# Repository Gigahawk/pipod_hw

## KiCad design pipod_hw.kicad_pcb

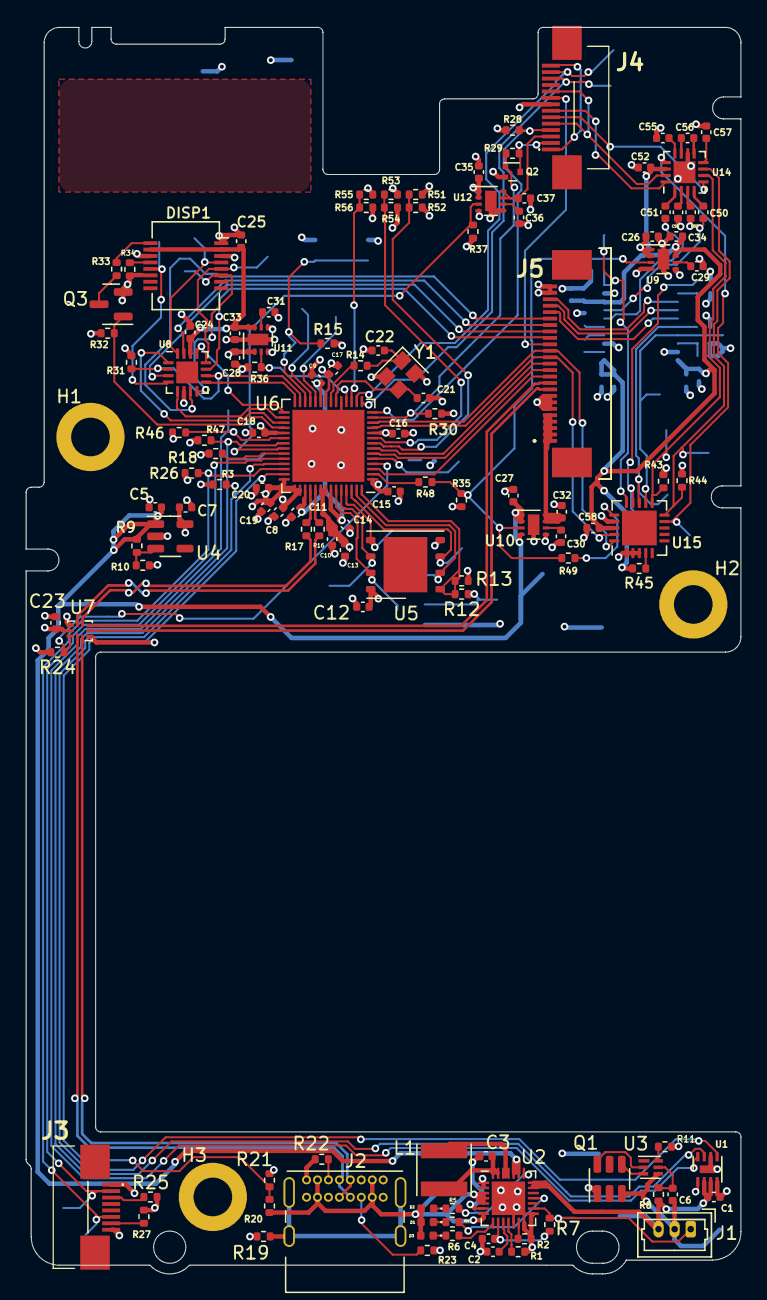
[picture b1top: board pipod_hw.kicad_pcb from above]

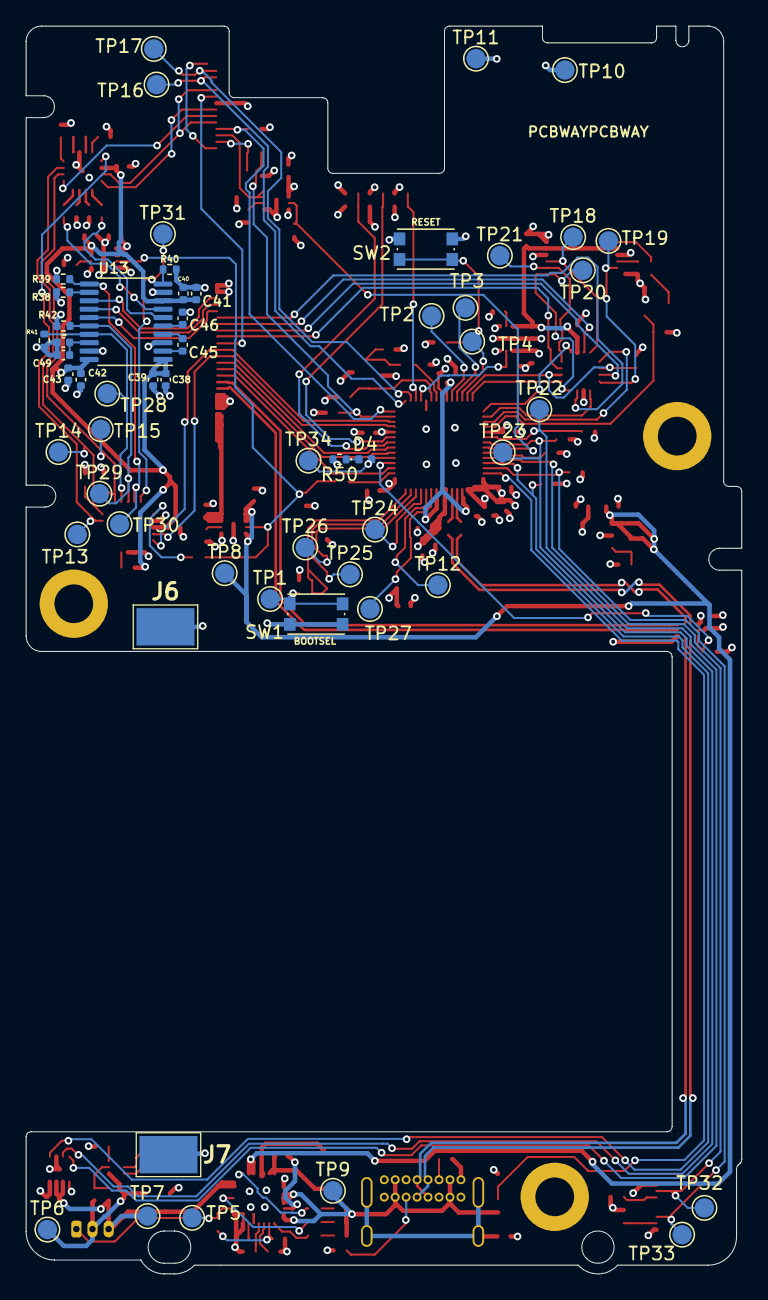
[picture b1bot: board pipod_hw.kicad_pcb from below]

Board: 4 copper layers, 55.5 x 96.8 mm, 184 parts (56 on the bottom side), 136 nets.

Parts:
C1, C3, C6, C8, C9, C10, C11, C12, C13, C15, C16, C17, C18, C19, C23, C24, C39, C41, C43, C49, C58: 100n; C_0402_1005Metric
C2: 150n; C_0402_1005Metric
C4, C14, C20, C50, C51, C53, C54, C55, C56, C57: 1u; C_0402_1005Metric
C5, C7, C25, C26, C27, C28, C32, C33, C34, C35, C37, C38, C40, C42, C48: 10u; C_0402_1005Metric
C21, C22: 30p; C_0402_1005Metric
C29, C30, C31, C36: DNI; C_0402_1005Metric
C45, C46, C52: 2.2u; C_0402_1005Metric
D1: RED; LED_0402_1005Metric
D2: BLU; LED_0402_1005Metric
D3, D4: GRN; LED_0402_1005Metric
DISP1: STP240320_0200B; Molex_SlimStack_54722-0164_2x08_P0.50mm_Vertical
H1, H2, H3: 9774040243R
J1: Conn_01x03_Male; Molex_PicoBlade_53047-0310_1x03_P1.25mm_Vertical
J2: USB_C_Receptacle_USB2.0; USB_C_Receptacle_GCT_USB4085
J3: SFV8R-2STE1HLF; SFV8R2STE1HLF
J4: SFV14R-2STE1HLF; SFV14R2STE1HLF
J5: 2-1734839-5; 217348395
J6, J7: S7051-42R; S705142R
L1: 1u; L_Vishay_IFSC-1515AH_4x4x1.8mm
LOGO1: Logo_Open_Hardware_Large; OSHW-Logo2_9.8x8mm_Mask
Q1: DMG9926UDM; SOT-23-6
Q2: NTK3139PT1G; SOT-723
Q3: BSS138; SOT-23
R1: 5.9k 2%; R_0402_1005Metric
R2: 1.6k; R_0402_1005Metric
R3, R7, R9, R13, R15, R18, R20, R24, R25, R27, R28, R30, R31, R32, R34, R35, R36, R37, R38, R39, R40, R41, R42, R43, R44, R45, R46, R47, R52, R54, R56: 10k; R_0402_1005Metric
R4, R5, R6, R12, R14, R48, R49: 1k; R_0402_1005Metric
R8: 330R; R_0402_1005Metric
R10, R29, R51, R53, R55: DNI; R_0402_1005Metric
R11: 2.2k; R_0402_1005Metric
R16, R17: 27R; R_0402_1005Metric
R19: DNP; R_0402_1005Metric
R21: 15k; R_0402_1005Metric
R22, R23: 5.1k; R_0402_1005Metric
R26: 100k; R_0402_1005Metric
R33: 10R; R_0402_1005Metric
R50: 470R; R_0402_1005Metric
SW1, SW2: SW_Push; SW_Push_1P1T_NO_CK_KMR2
TP1, TP2, TP3, TP4, TP5, TP6, TP7, TP8, TP9, TP10, TP11, TP12, TP13, TP14, TP15, TP16, TP17, TP18, TP19, TP20, TP21, TP22, TP23, TP24, TP25, TP26, TP27, TP28, TP29, TP30, TP31, TP32, TP33, TP34: TestPoint; TestPoint_Pad_D1.5mm
U1: MAX17048G+T10; DFN-8-1EP_2x2mm_P0.5mm_EP0.6x1.2mm
U2: MAX8903AETI+T; QFN-28-1EP_4x4mm_P0.4mm_EP2.6x2.6mm
U3: BQ29728DSER; WSON-6_1.5x1.5mm_P0.5mm
U4: XC6210B332MR; SOT-23-5
U5: W25Q128JVS; WSON-8-1EP_6x5mm_P1.27mm_EP3.4x4.3mm
U6: RP2040; QFN-56-1EP_7x7mm_P0.4mm_EP5.6x5.6mm
U7: NLAS7242MUTBG; UQFN-10_1.4x1.8mm_P0.4mm
U8: RS2299XTQC16; QFN-16-1EP_3x3mm_P0.5mm_EP1.7x1.7mm
U9, U10, U11, U12: TPS22965TDSGRQ1; WSON-8-1EP_2x2mm_P0.5mm_EP0.9x1.6mm
U13: PCM5102APWR; TSSOP-20_4.4x6.5mm_P0.65mm
U14: PAM8908JER; QFN-16-1EP_3x3mm_P0.5mm_EP1.7x1.7mm
U15: MCP23008-E/ML; QFN-20-1EP_4x4mm_P0.5mm_EP2.7x2.7mm
Y1: 12MHz 20pF; Crystal_SMD_2520-4Pin_2.5x2.0mm

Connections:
+1V1: C9.2, C11.2, C14.2, U6.23 (DVDD), U6.45 (VREG_VOUT), U6.50 (DVDD)
+3V3: C7.1, C8.2, C10.2, C12.2, C13.2, C15.2, C16.2, C17.2, C18.2, C19.2, C20.2, C23.1, C26.2, C28.2, C35.2, J3.1, Q2.2 (S), R3.1, R13.2, R15.1, R24.2, R25.2, R26.2, R27.2, R28.2, R30.1, R46.1, R47.1, R51.1, R53.1, R55.1, TP10.1, U4.5 (VOUT), U5.8 (VCC), U6.1 (IOVDD), U6.10 (IOVDD), U6.22 (IOVDD), U6.33 (IOVDD), U6.42 (IOVDD), U6.43 (ADC_AVDD), U6.44 (VREG_IN), U6.48 (USB_VDD), U6.49 (IOVDD), U7.9 (VCC), U9.1 (VIN), U9.2 (VIN), U9.4 (VBIAS), U11.1 (VIN), U11.2 (VIN), U11.4 (VBIAS), U12.1 (VIN), U12.2 (VIN), U12.4 (VBIAS)
+BATT: C1.2, J1.3, R8.1, TP7.1, U1.2 (CELL), U1.3 (VDD), U2.20 (BAT), U2.21 (BAT)
-BATT: C6.2, J1.2, Q1.3 (S2), TP6.1, U3.4 (VSS)
/Audio/AMP_CAP+: C56.1, U14.11 (CAP+)
/Audio/AMP_CAP-: C56.2, U14.9 (CAP-)
/Audio/AMP_HPVDD: C55.2, U14.12 (HPVDD)
/Audio/AMP_HPVSS: C57.1, U14.8 (HPVSS)
/Audio/AMP_INL+: C54.2, U14.2 (INL+)
/Audio/AMP_INL-: C51.2, U14.1 (INL-)
/Audio/AMP_INR+: C53.2, U14.3 (INR+)
/Audio/AMP_INR-: C50.2, U14.4 (INR-)
/Audio/DAC_CAPM: C45.2, U13.4 (CAPM)
/Audio/DAC_CAPP: C45.1, U13.2 (CAPP)
/Audio/DAC_LDOO: C48.1, C49.1, U13.18 (LDOO)
/Audio/DAC_SCK: R38.2, U13.12 (SCK)
/Audio/DAC_VNEG: C46.1, U13.5 (VNEG)
/Display/DISP_BL_MOS_D: Q3.3 (D), R33.1
/Display/DISP_CS: DISP1.8 (CS), R34.1
/Display/DISP_LEDK: DISP1.2 (LEDK), R33.2
/Headphone/HP_CLICKER_SPEAKER: J4.2, Q2.3 (D), R29.2
/Load Switches/AUDIO_SW_CT: C29.2, U9.6 (CT)
/Load Switches/DISP_SW_CT: C31.2, U11.6 (CT)
/Load Switches/PI_SW_CT: C30.2, U10.6 (CT)
/Load Switches/RMT_SW_CT: C36.2, U12.6 (CT)
/Pi/PI_VCC_LATCH: R49.1, U15.16 (GP7)
/Pi/~IO_EX_RST: R45.2, U15.4 (~RESET)
/Power/CHRG_BST: C3.2, U2.6 (BST)
/Power/CHRG_CS: L1.1, U2.25 (CS), U2.26 (CS)
/Power/CHRG_CURR_SET: R2.2, U2.13 (ISET)
/Power/CHRG_DOK_LEDK: D3.1 (K), R6.1
/Power/CHRG_FLT_LEDK: D1.1 (K), R4.1
/Power/CHRG_IN_CURR_SET: R1.2, U2.11 (IDC)
/Power/CHRG_LEDK: D2.1 (K), R5.1
/Power/CHRG_LX: C3.1, L1.2, U2.27 (LX), U2.28 (LX)
/Power/CHRG_TIMER_SET: C2.2, U2.10 (CT)
/Power/CHRG_VL: C4.2, R7.1, U2.9 (VL)
/Power/PROT_BAT+: C6.1, R8.2, U3.5 (BAT)
/Power/PROT_C: Q1.6 (G1), U3.2 (Cout)
/Power/PROT_D: Q1.4 (G2), U3.3 (Dout)
/Power/PROT_V-: R11.2, U3.6 (V-)
/SMC/PI_VCC_EN: R48.2, U6.2 (GPIO0)
/SMC/SMC_SWCLK: TP2.1, U6.24 (SWCLK)
/SMC/SMC_SWD: TP3.1, U6.25 (SWD)
/SMC/SMC_USB_D+: R16.2, U6.47 (USB_DP)
/SMC/SMC_USB_D-: R17.2, U6.46 (USB_DM)
/SMC/SMC_XIN: C21.2, U6.20 (XIN), Y1.3
/SMC/SMC_XOUT: R14.1, U6.21 (XOUT)
/SMC/SMC_XOUT_ATTN: C22.1, R14.2, Y1.1
/SMC/~SMC_CW_CS: R18.1, U6.37 (GPIO25)
/SMC/~SMC_USB_BOOT: R12.1, SW1.2, TP1.1
/USB/USB_SHIELD: J2.S1 (SHIELD), R19.2
AUDIO_3V3: C34.2, C38.1, C39.1, C40.1, C41.1, C42.1, C43.1, C52.2, C58.2, R45.1, U9.7 (VOUT), U9.8 (VOUT), U13.1 (CPVDD), U13.8 (AVDD), U13.20 (DVDD), U14.14 (PVDD), U15.18 (VDD)
CW_EN1: J3.3, R25.1
CW_EN2: J3.7, R27.1
DAC_OUTL: C51.1, U13.6 (OUTL)
DAC_OUTR: C50.1, U13.7 (OUTR)
DISP_3V3: C24.2, C25.1, C33.2, DISP1.3 (LEDA), DISP1.4 (VCC), U8.14 (V+), U11.7 (VOUT), U11.8 (VOUT)
DISP_3V3_EN: R36.2, U6.18 (GPIO15), U11.3 (ON)
DISP_DC: DISP1.7 (WR/A0), TP18.1, U8.16 (COM1)
DISP_INPUT_SEL: R31.2, U6.27 (GPIO16), U8.2 (IN12), U8.10 (IN34)
DISP_MOSI: DISP1.10 (SDA), TP19.1, U8.4 (COM2)
DISP_RST: DISP1.11 (RESET), TP20.1, U8.8 (COM3)
DISP_SCK: DISP1.9 (RS/SCL), TP21.1, U8.12 (COM4)
GND: C1.1, C2.1, C4.1, C5.1, C7.2, C8.1, C9.1, C10.1, C11.1, C12.1, C13.1, C14.1, C15.1, C16.1, C17.1, C18.1, C19.1, C20.1, C21.1, C22.2, C23.2, C24.1, C25.2, C26.1, C27.1, C28.1, C29.1, C30.1, C31.1, C32.1, C33.1, C34.1, C35.1, C36.1, C37.1, C38.2, C39.2, C40.2, C41.2, C42.2, C43.2, C46.2, C48.2, C49.2, C52.1, C53.1, C54.1, C55.1, C57.2, C58.1, DISP1.1 (GND), DISP1.5 (GND), DISP1.6 (GND), DISP1.12 (GND), H1.1, H2.1, H3.1, J2.A1 (GND), J2.A12 (GND), J2.B1 (GND), J2.B12 (GND), J3.8, J4.8, J5.6, J5.7, J5.8, J5.24, J5.25, J6.1, J7.1, Q1.1 (D1), Q3.2 (S), R1.1, R2.1, R10.1, R11.1, R18.2, R19.1, R21.2, R22.2, R23.2, R31.1, R32.1, R34.2, R35.1, R36.1, R37.1, R38.1, R39.1, R40.1, R41.1, R42.1, R43.1, R44.1, R50.2, R52.2, R54.2, R56.2, SW1.1, SW2.1, TP11.1, U1.1 (CTG), U1.4 (GND), U1.6 (QSTRT), U1.9 (EP), U2.1 (PG), U2.2 (PG), U2.12 (GND), U2.14 (~CEN), U2.15 (USUS), U2.29 (EP), U4.2 (GND), U5.4 (GND), U6.19 (TESTEN), U6.57 (GND), U7.3 (GND), U7.8 (~OE), U8.6 (GND), U9.5 (GND), U9.9 (EP), U10.5 (GND), U10.9 (EP), U11.5 (GND), U11.9 (EP), U12.5 (GND), U12.9 (EP), U13.3 (CPGND), U13.9 (AGND), U13.19 (DGND), U14.10 (PGND), U14.17 (EPAD), U15.1 (A2), U15.2 (A1), U15.3 (A0), U15.17 (VSS), Y1.2, Y1.4
GNDA: J4.5, J4.10, U14.15 (SGND)
HP_CLICKER: Q2.1 (G), R29.1, R30.2, U6.13 (GPIO10)
HP_LCK: J4.4, R28.1, U6.14 (GPIO11)
HP_R1_R: J4.6, U14.5 (OUTR)
HP_RMT4_3V3: C37.2, J4.3, U12.7 (VOUT), U12.8 (VOUT)
HP_SHIELD: J4.1, J4.14
HP_SL_VIDEO: J4.9, J5.16
HP_T_L: J4.7, U14.16 (OUTL)
HWID0: R51.2, R52.1, U6.8 (GPIO6)
HWID1: R53.2, R54.1, U6.9 (GPIO7)
HWID2: R55.2, R56.1, U6.17 (GPIO14)
MCU_RUN: R15.2, SW2.2, TP4.1, U6.26 (RUN)
NTC: J1.1, R7.2, TP5.1, U2.16 (THM)
unnamed: D4.1 (K), R50.1
PI_AMP_EN: TP13.1, U14.13 (EN), U15.9 (GP0)
PI_AMP_G0: R43.2, TP15.1, U14.6 (G0), U15.11 (GP2)
PI_AMP_G1: R44.2, TP14.1, U14.7 (G1), U15.10 (GP1)
PI_DAC_DEMP: R40.2, TP31.1, U13.10 (DEMP), U15.15 (GP6)
PI_DAC_FLT: R39.2, TP30.1, U13.11 (FLT), U15.14 (GP5)
PI_DAC_FMT: R42.2, TP29.1, U13.16 (FMT), U15.13 (GP4)
PI_DAC_XSMT: R41.2, TP28.1, U13.17 (XSMT), U15.12 (GP3)
PI_DISP_DC: J5.19, U8.15 (NO1)
PI_DISP_MOSI: J5.18, U8.3 (NO2)
PI_DISP_RST: J5.20, U8.7 (NO3)
PI_DISP_SCK: J5.17, U8.11 (NO4)
PI_I2S_BCK: J5.23, U13.13 (BCK)
PI_I2S_DIN: J5.22, U13.14 (DIN)
PI_I2S_LRCK: J5.21, U13.15 (LRCK)
PI_LOAD_SWITCH_EN: R35.2, R48.1, R49.2, U9.3 (ON), U10.3 (ON)
PI_USB_MUXED_D+: J5.10, U7.5 (HSD1+)
PI_USB_MUXED_D-: J5.9, U7.4 (HSD1-)
PI_VCC: C32.2, J5.1, J5.2, J5.3, J5.4, J5.5, U10.7 (VOUT), U10.8 (VOUT)
REG_CE: R9.1, R10.2, U4.3 (CE)
RMT_3V3_EN: R37.2, U6.36 (GPIO24), U12.3 (ON)
SMC_CW_MOSI: J3.6, R26.1, TP33.1, U6.40 (GPIO28_ADC2)
SMC_CW_SCK: J3.2, TP32.1, U6.38 (GPIO26_ADC0)
SMC_DISP_BL: Q3.1 (G), R32.2, U6.32 (GPIO21)
SMC_DISP_DC: U6.31 (GPIO20), U8.1 (NC1)
SMC_DISP_MOSI: U6.30 (GPIO19), U8.5 (NC2)
SMC_DISP_RST: U6.28 (GPIO17), U8.9 (NC3)
SMC_DISP_SCK: U6.29 (GPIO18), U8.13 (NC4)
SMC_I2C_SCL: R47.2, TP23.1, U1.7 (SCL), U6.35 (GPIO23)
SMC_I2C_SDA: R46.2, TP22.1, U1.8 (SDA), U6.34 (GPIO22)
SMC_INT: J5.11, U6.3 (GPIO1)
SMC_LED: D4.2 (A), TP34.1, U6.5 (GPIO3)
SMC_PI_I2C_SCL: J5.15, U6.12 (GPIO9), U15.20 (SDA)
SMC_PI_I2C_SDA: J5.14, U6.11 (GPIO8), U15.19 (SCL)
SMC_QSPI_SCLK: TP12.1, U5.6 (CLK), U6.52 (QSPI_SCLK)
SMC_QSPI_SD0: TP24.1, U5.5 (DI(IO0)), U6.53 (QSPI_SD0)
SMC_QSPI_SD1: TP25.1, U5.2 (DO(IO1)), U6.55 (QSPI_SD1)
SMC_QSPI_SD2: TP26.1, U5.3 (IO2), U6.54 (QSPI_SD2)
SMC_QSPI_SD3: TP27.1, U5.7 (IO3), U6.51 (QSPI_SD3)
SMC_RMT_RX: J4.13, TP17.1, U6.16 (GPIO13)
SMC_RMT_TX: J4.12, TP16.1, U6.15 (GPIO12)
SMC_RX_PI_TX: J5.13, U6.7 (GPIO5)
SMC_TX_PI_RX: J5.12, U6.6 (GPIO4)
SMC_USB_MUXED_D+: R16.1, U7.7 (HSD2+)
SMC_USB_MUXED_D-: R17.1, U7.6 (HSD2-)
USB_CC1: J2.A5 (CC1), R22.1
USB_CC2: J2.B5 (CC2), R23.1
USB_D+: J2.A6 (D+), J2.B6 (D+), U7.1 (D+)
USB_D-: J2.A7 (D-), J2.B7 (D-), U7.2 (D-)
USB_DET: R20.2, R21.1, U6.41 (GPIO29_ADC3)
USB_MUX_SEL: R24.1, U6.4 (GPIO2), U7.10 (S)
VBUS: D1.2 (A), D2.2 (A), D3.2 (A), J2.A4 (VBUS), J2.A9 (VBUS), J2.B4 (VBUS), J2.B9 (VBUS), R20.1, TP9.1, U2.3 (DC), U2.4 (DC), U2.5 (DCM), U2.7 (IUSB)
VCC: C5.2, C27.2, R9.2, TP8.1, U2.23 (SYS), U2.24 (SYS), U4.1 (VIN), U10.1 (VIN), U10.2 (VIN), U10.4 (VBIAS)
~CHRG_DOK: R6.2, U2.8 (~DOK)
~CHRG_FLT: R4.2, U2.18 (~FLT)
~CHRG: R5.2, U2.22 (~CHG)
~FG_ALRT: R3.2, U1.5 (~ALRT), U6.39 (GPIO27_ADC1)
~SMC_QSPI_SS: R12.2, R13.1, U5.1 (~CS), U6.56 (~QSPI_SS)

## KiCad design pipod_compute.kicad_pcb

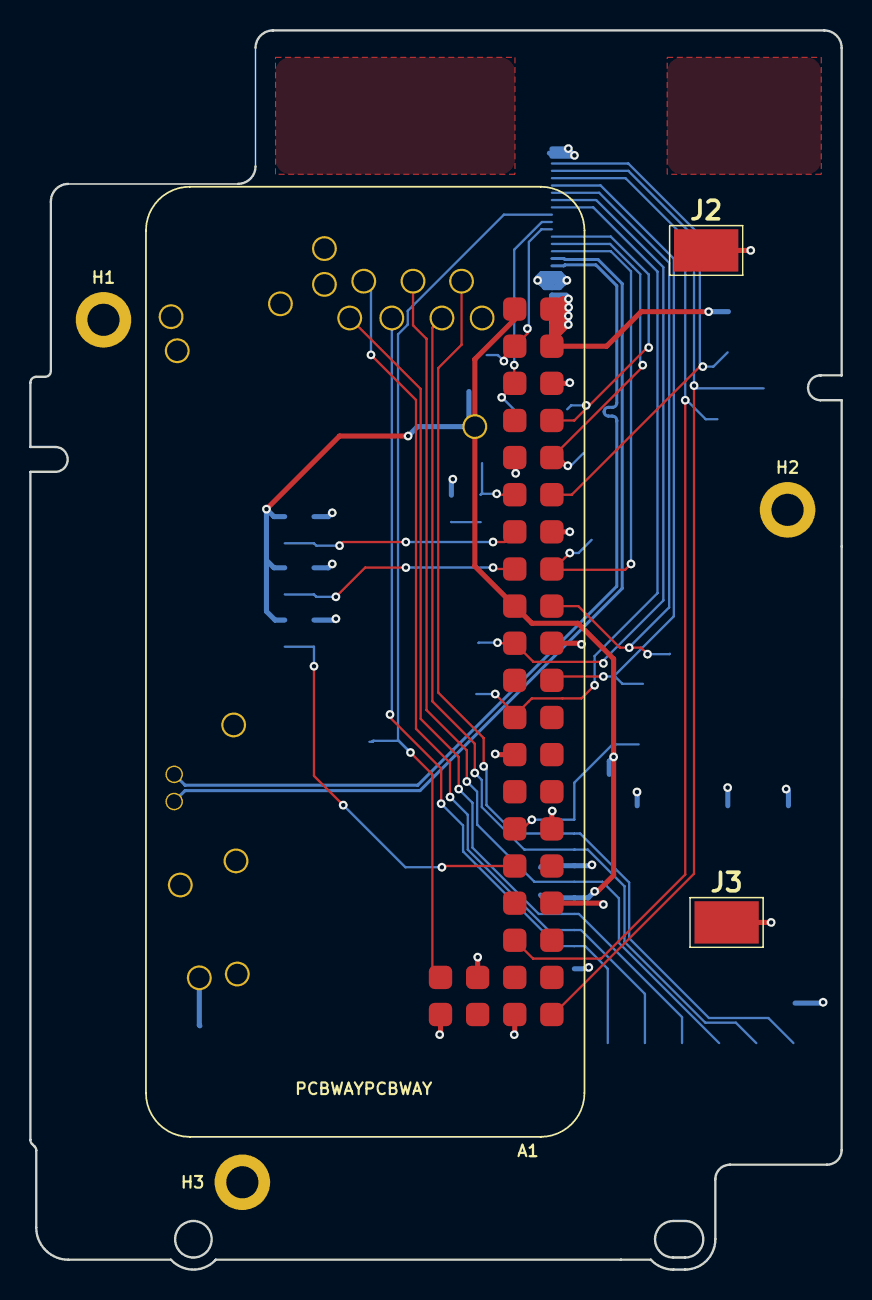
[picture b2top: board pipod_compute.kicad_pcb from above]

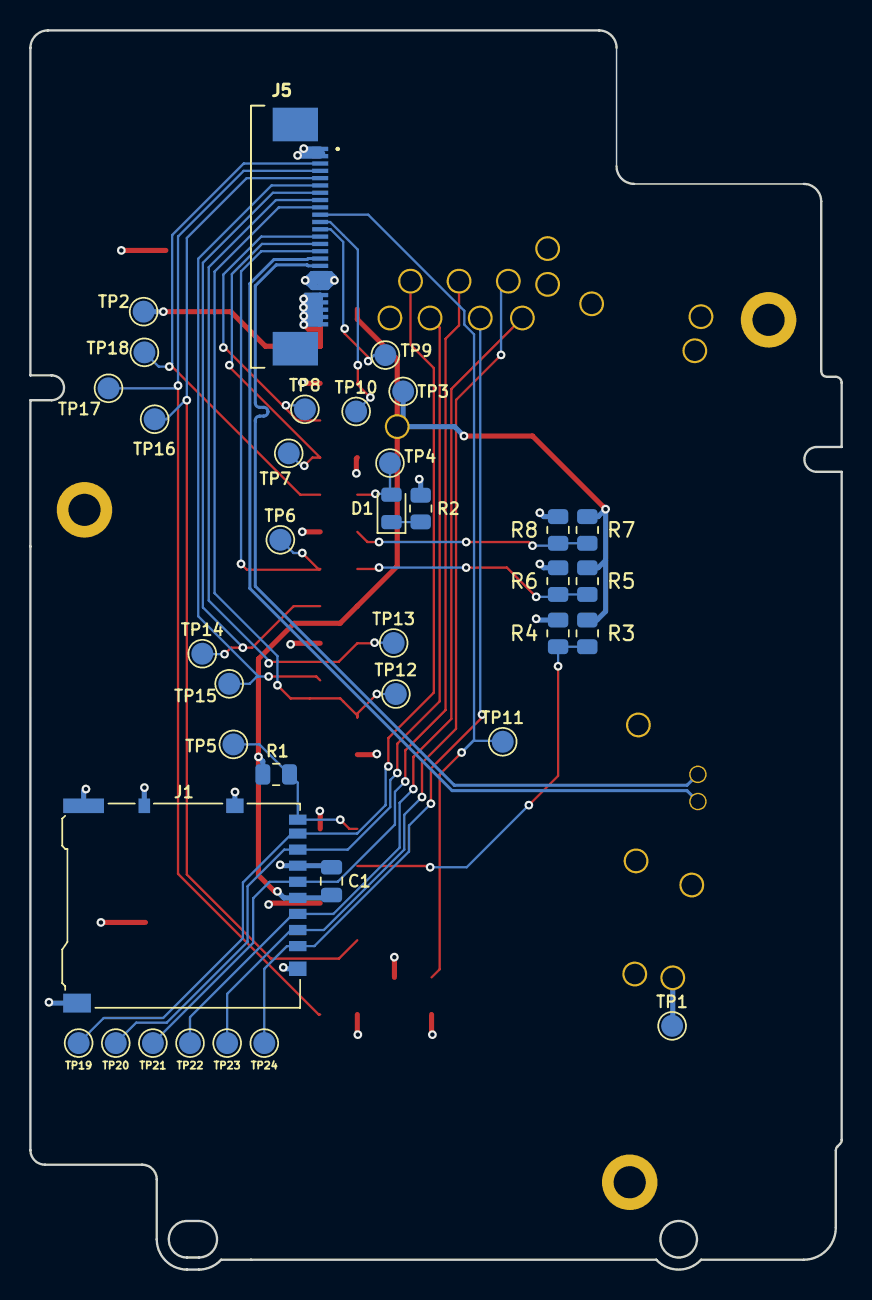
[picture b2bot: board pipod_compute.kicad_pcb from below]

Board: 4 copper layers, 55.5 x 84.8 mm, 43 parts (36 on the bottom side), 30 nets.

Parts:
A1: RASPBERRY_PI_ZERO_SMT; RASPI_ZERO_1_3_SMT_LOW_PROFILE
C1: 10u; C_0805_2012Metric
D1: GRN; LED_0805_2012Metric
H1, H2, H3: MountingHole_Pad; MountingHole_2.2mm_M2_DIN965_Pad
J1: Micro_SD_Card; microSD_HC_Hirose_DM3AT-SF-PEJM5
J2, J3: S7041-42R
J5: 2-1734839-5; 217348395
LOGO1: Logo_Open_Hardware_Large; OSHW-Logo2_9.8x8mm_Mask
R1, R4, R6, R8: 10k; R_0805_2012Metric
R2: 470R; R_0805_2012Metric
R3, R5, R7: DNI; R_0805_2012Metric
TP1, TP2, TP3, TP4, TP5, TP6, TP7, TP8, TP9, TP10, TP11, TP12, TP13, TP14, TP15, TP16, TP17, TP18, TP19, TP20, TP21, TP22, TP23, TP24: TestPoint; TestPoint_Pad_D1.5mm

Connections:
+3V3: A1.1 (3V3), A1.17 (3V3), A1.PP8 (3V3), C1.2, J1.4 (VDD), R1.2, R3.1, R5.1, R7.1, TP3.1
GND: A1.6 (GND), A1.9 (GND), A1.14 (GND), A1.20 (GND), A1.25 (GND), A1.30 (GND), A1.34 (GND), A1.39 (GND), A1.PP5 (GND), A1.PP6 (GND), A1.PP35 (GND), A1.RUN1 (GND), A1.TV2 (GND), C1.1, H1.1, H2.1, H3.1, J1.6 (VSS), J1.10 (DET_A), J1.11 (SHIELD), J2.1, J3.1, J5.1, J5.2, J5.18, J5.19, J5.20, R2.1, R4.2, R6.2, R8.2, TP1.1
HP_SL_VIDEO: A1.TV1 (TV), J5.10, TP11.1
HWID0: A1.31 (GPIO6), R3.2, R4.1
HWID1: A1.15 (GPIO22), R5.2, R6.1
HWID2: A1.13 (GPIO27), R7.2, R8.1
unnamed: A1.11 (GPIO17), D1.2 (A), TP4.1
unnamed: D1.1 (K), R2.2
PI_DISP_DC: A1.18 (GPIO24), J5.7, TP14.1
PI_DISP_MOSI: A1.19 (GPIO10/MOSI), J5.8, TP13.1
PI_DISP_RST: A1.22 (GPIO25), J5.6, TP15.1
PI_DISP_SCK: A1.23 (GPIO11/SCLK), J5.9, TP12.1
PI_I2S_BCK: A1.12 (GPIO18/PCM_CLK), J5.3, TP18.1
PI_I2S_DIN: A1.40 (GPIO21/PCM_DOUT), J5.4, TP17.1
PI_I2S_LRCK: A1.35 (GPIO19/PCM_FS), J5.5, TP16.1
PI_USB_MUXED_D+: A1.PP22 (USB_D+), J5.16
PI_USB_MUXED_D-: A1.PP23 (USB_D-), J5.17
SD_CD: A1.PP19 (SD_CD), J1.2 (DAT3/CD), TP23.1
SD_CLK: A1.PP14 (SD_CLK), J1.5 (CLK), TP21.1
SD_CMD: A1.PP15 (SD_CMD), J1.3 (CMD), TP22.1
SD_DAT0: A1.PP16 (SD_DAT0), J1.7 (DAT0), TP20.1
SD_DAT1: A1.PP17 (SD_DAT1), J1.8 (DAT1), TP19.1
SD_DAT2: A1.PP18 (SD_DAT2), J1.1 (DAT2), TP24.1
SD_DET: A1.29 (GPIO5), J1.9 (DET_B), R1.1, TP5.1
SMC_INT: A1.16 (GPIO23), J5.15, TP6.1
SMC_PI_I2C_SCL: A1.5 (GPIO3/SCL), J5.11, TP10.1
SMC_PI_I2C_SDA: A1.3 (GPIO2/SDA), J5.12, TP9.1
SMC_RX_PI_TX: A1.8 (GPIO14/TXD), J5.13, TP8.1
SMC_TX_PI_RX: A1.10 (GPIO15/RXD), J5.14, TP7.1
VCC: A1.2 (5V), A1.4 (5V), J5.21, J5.22, J5.23, J5.24, J5.25, TP2.1

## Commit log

2022-08-23 layout: copy layout from clickwheel breakout
2022-08-25 drc: set DRC for JLCPCB
2022-08-25 schem: add LCSC lib, import DW01A
2022-08-25 schem: add battery protection
2022-08-30 analysis: determine TEMP resistors
2022-08-30 schem: add battery charging, charger isolation
2022-08-31 analysis: determine LDO resistors
2022-08-31 schem: finish power design, start SMC design
2022-09-03 analysis: add notes on display mux
2022-09-03 analysis: describe SMC bus layout
2022-09-06 analysis: add documentation on load switches
2022-09-06 schem: digital design first pass
2022-09-07 schem: first pass done, ERC passing
2022-09-27 analysis: specify pi will be powered directly from VCC
2022-09-27 analysis: change system regulator to one with lower dropout
2022-09-30 schem: add MOSFET to drive clickwheel
2022-09-30 analysis: discuss mounting hardware
2022-09-30 layout: switch to lcsc fpc connectors
2022-10-03 integration: add mounting holes and connectors and second board
2022-10-04 analysis: decide on vendor
2022-10-04 schem: migrate away from LCSC exclusive parts
    - layout: migrate away from lcsc footprints
2022-10-05 layout: update footprint for TP4056M
2022-10-17 analysis: add calculation for USB differential impedance
2022-10-17 analysis: add calculation for battery protection
2022-10-17 analysis: remove thermistor calculations, switched to MAX8903
2022-10-17 analysis: add 0.2mm gap calculation for usb impedance
2022-10-18 layout: preliminary layout of most of board
2022-11-07 routing: begin routing
2022-11-08 routing: finish routing (board is not manufacturable)
2022-11-09 analysis: add usb impedance calc for 0.16mm track spacing
2022-11-09 layout, routing: relayout and reroute board
2022-11-10 layout: add testpoints, extra mounting hole, grounding clips
2022-11-17 layout: cleanup silkscreen, add bootloader buttons
2022-11-18 analysis: add notes on allowing pi to latch its own power
2022-11-18 schematic: add resistors to allow latching pi power
2022-11-22 compute: finish layout and routing
2022-11-24 ci: prepare files for CI
2022-11-24 ci: add ci scripts
2022-11-24 compute: update constraints to match cheaper pcbway tier
2022-11-24 smc: update constraints to match cheaper pcbway tier
2022-11-24 ci: count SMD and THT parts in BOM
2022-11-24 ci: export footprint type and side in bom
2022-11-24 ci: enable pcb and stats info in BOM
2022-11-24 ci: add footprint populate column to BOM
2022-11-25 ci: add filter for only SMD components
2022-11-25 Revert "ci: add filter for only SMD components"
    This reverts commit a0d158252d78596f62362f8a0a8bbaafcbc1603f.
2022-11-25 ci: test marking parts in sch for bom
2022-11-25 ci: remove populate column
2022-11-25 gitignore: ignore project backups
2022-11-25 ci: add vendor/distributor part numbers to bom
2022-11-25 ci: enable bom quantity
2022-11-25 ci: rename jlcpcb outputs to pcbway, enable boardview output
2022-11-25 bugfix: enable all copper layers in CI export
2022-11-25 layout: add OSHW logo, change version text to masked copper
2022-11-25 compute: fill out bom columns
2022-12-23 feature: add hardware ID resistors
